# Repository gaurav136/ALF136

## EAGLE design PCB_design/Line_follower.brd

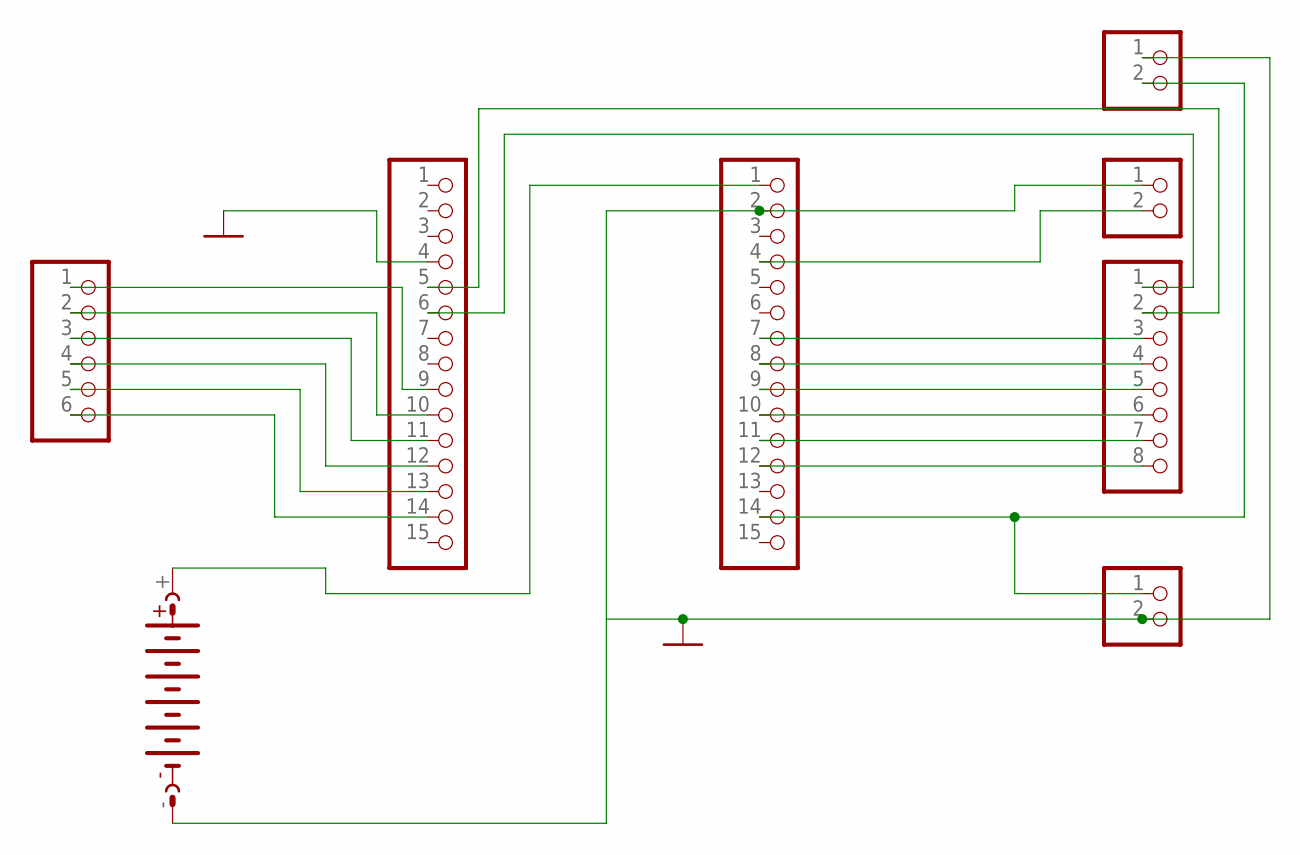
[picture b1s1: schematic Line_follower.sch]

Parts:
G1: AB9V
JP1, JP2: PINHD-1X15; 1X15
JP3: PINHD-1X8; 1X08
JP4: PINHD-1X6; 1X06
JP5, JP6, JP7: PINHD-1X2; 1X02

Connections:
GND: G1.-, JP1.4, JP2.2, JP5.1, JP6.2, JP7.1
unnamed: JP1.14, JP4.6
unnamed: JP1.13, JP4.5
unnamed: JP1.12, JP4.4
unnamed: JP1.11, JP4.3
unnamed: JP1.10, JP4.2
unnamed: JP1.9, JP4.1
unnamed: JP2.12, JP3.8
unnamed: JP2.11, JP3.7
unnamed: JP2.10, JP3.6
unnamed: JP2.9, JP3.5
unnamed: JP2.8, JP3.4
unnamed: JP2.7, JP3.3
unnamed: JP1.5, JP3.2
unnamed: JP2.4, JP7.2
unnamed: JP2.14, JP5.2, JP6.1
unnamed: G1.+, JP2.1
unnamed: JP1.6, JP3.1

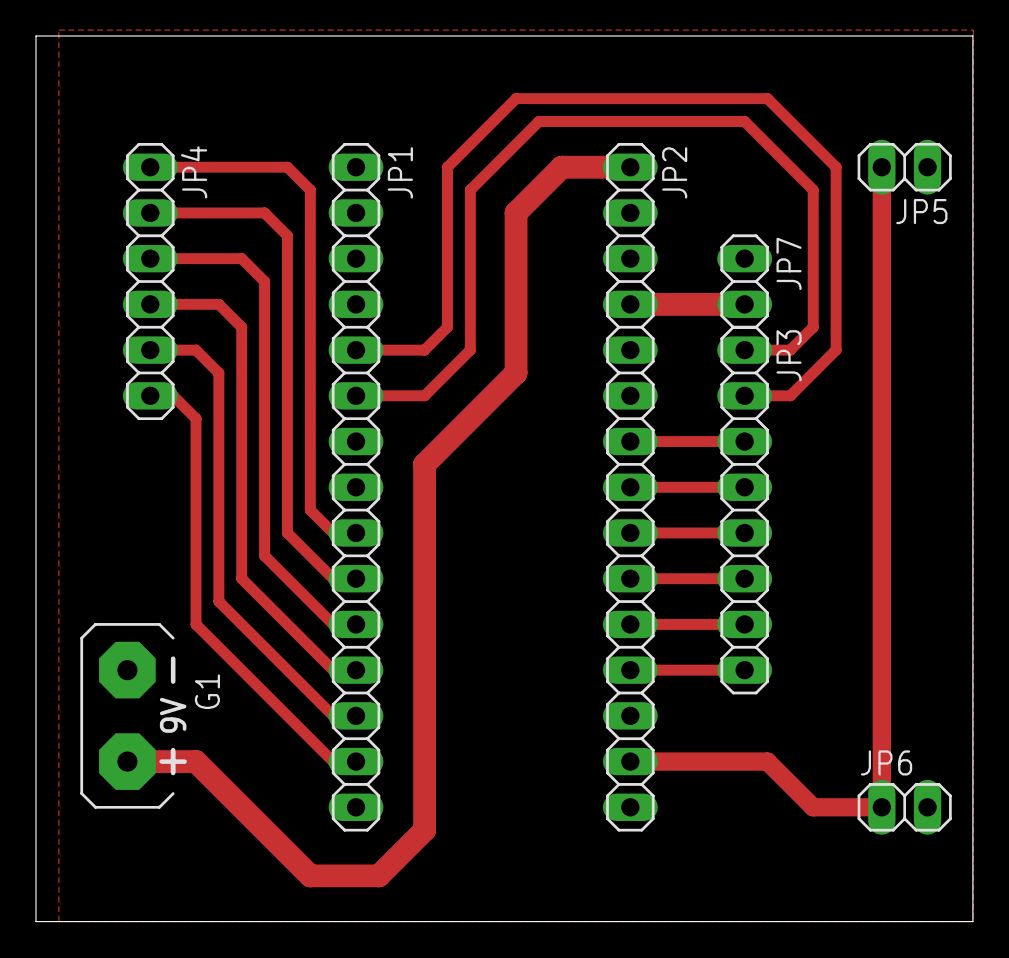
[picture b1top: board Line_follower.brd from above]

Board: 2 copper layers, 52.1 x 49.2 mm, 8 parts (0 on the bottom side), 18 nets.

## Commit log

2024-01-09 T junction with extra ir
2024-01-09 QR gen using OpenCV
2024-01-09 websocket
2024-01-10 OpenCV + websocket on replit
2024-01-10 replit javascript server reciver
2024-01-10 PCB design of ALF
2024-01-10 Doc of IARC
2024-01-10 Bot image
2024-09-08 feat : gui for image detection
2024-09-08 Add files via upload
    backup tushar code
2024-09-08 Add files via upload
    feat : maze solver
